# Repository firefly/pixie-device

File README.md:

Firefly Pixie: Hardware
=======================

The hardware design, schematics and PCB layouts for the Firefly
Pixie Hardware Wallet for Ethereum (and ilk).

- [Firmware](https://github.com/firefly/pixie-firmware)
- [Case](https://github.com/firefly/pixie-case)

See the [CHANGELOG](./CHANGELOG.md) for high-level changes
between board revisions.

Tech Specs
----------

- **Processor:** ESP32-C3 (32-bit RISC-V)
- **Speed:** 160Mhz
- **Memory:** 400kb RAM, 16Mb Flash, 4kb eFuse
- **Inputs:** 4x tactile buttons
- **Outputs:**
  - 240x240px IPS 1.3" display (16-bit color; RGB565)
  - 4x RGB LED (WS2812B; 24-bit color; GRB888)
- **Connectivity:**
  - USB-C (power + JTAG/CDC-ACM)
  - BLE

Contributing
------------

- To modify the files, use [KiCad](https://www.kicad.org) (open-source EDA application)
- Since the `git diff` involved in modifying these files is somewhat opaque, please start a discussion first, so any changes can be coordinated

Photos
-----------

See the [output](./output/) folder for rendered schematics, PCBs
and 3D renders along with photos of the various revisions.

License
-------

MIT License.

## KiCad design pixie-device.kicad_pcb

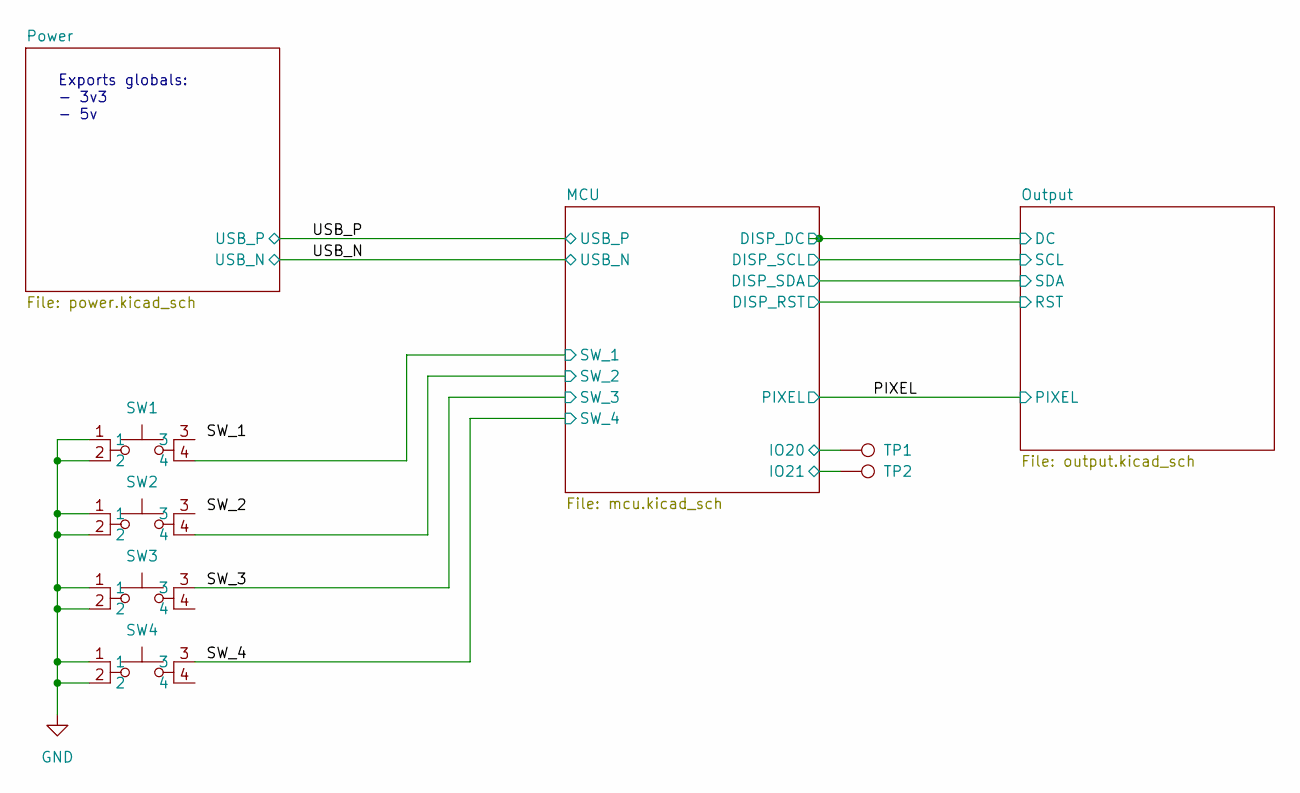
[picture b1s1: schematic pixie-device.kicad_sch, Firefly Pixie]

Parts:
SW1, SW2, SW3, SW4: button-oval; MPN C720479
TP1, TP2: TestPoint; TestPoint_Pad_D1.0mm

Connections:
/MCU/IO20: TP1.1; also elsewhere on the board
/MCU/IO21: TP2.1; also elsewhere on the board
/MCU/SW_1: SW1.4; also elsewhere on the board
/MCU/SW_2: SW2.4; also elsewhere on the board
/SW_3: SW3.3; also elsewhere on the board
/SW_4: SW4.3; also elsewhere on the board
GND: SW1.1, SW1.2, SW2.1, SW2.2, SW3.1, SW3.2, SW4.1, SW4.2; also elsewhere on the board

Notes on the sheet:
Exports globals: - 3v3 - 5v

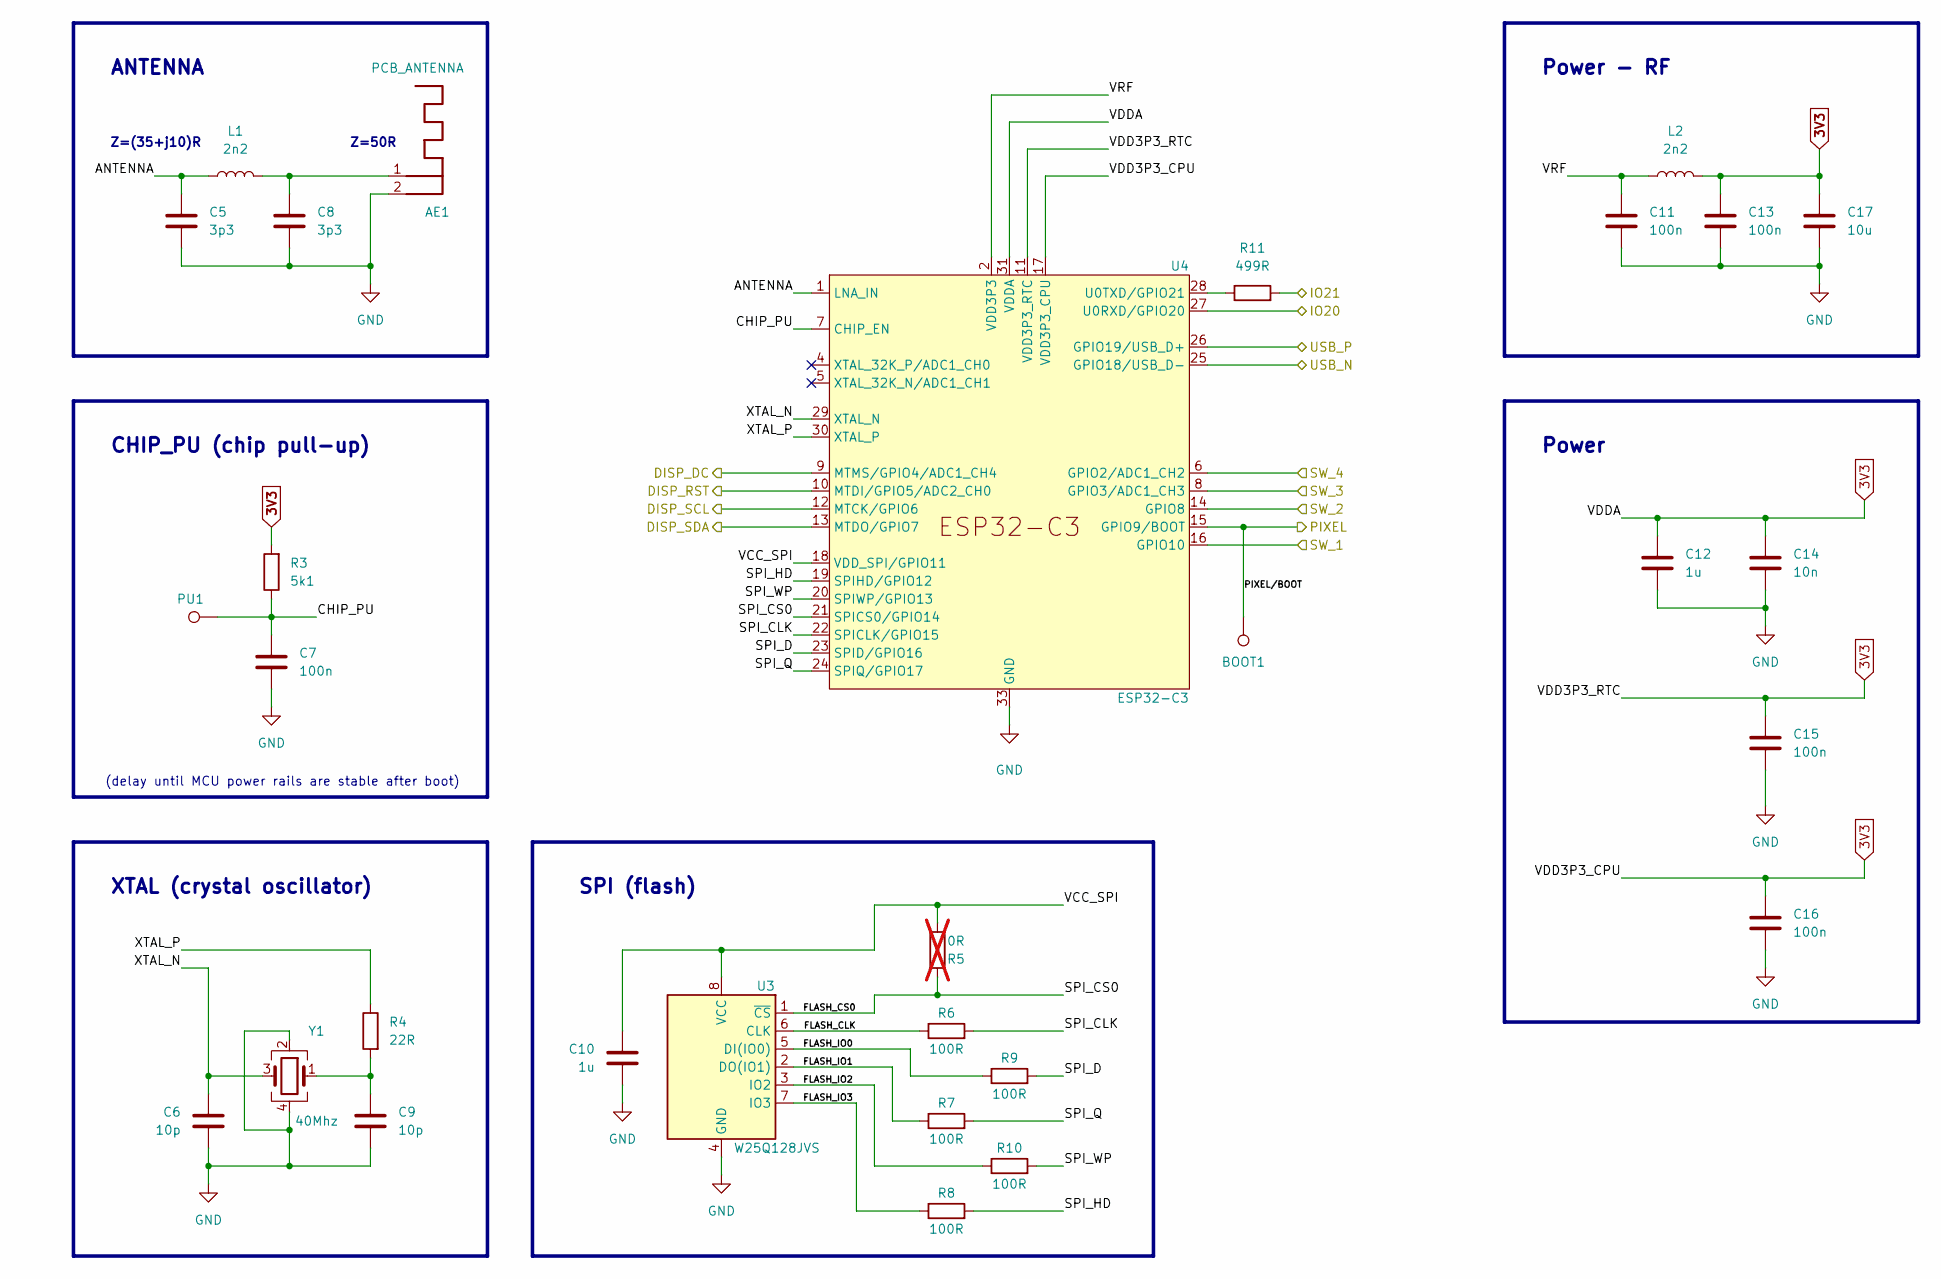
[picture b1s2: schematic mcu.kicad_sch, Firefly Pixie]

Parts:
AE1: PCB_ANTENNA; PCB_Antenna
BOOT1: TestPoint; TestPoint_Pad_D1.0mm
C5, C8: 3p3; C_0201_0603Metric; MPN C258460
C6, C9: 10p; C_0201_0603Metric; MPN C272871
C7, C11, C13, C15, C16: 100n; C_0201_0603Metric; MPN C284966
C10, C12: 1u; C_0201_0603Metric; MPN C170153
C14: 10n; C_0201_0603Metric; MPN C76941
C17: 10u; C_0402_1005Metric; MPN C315248
L1, L2: 2n2; L_0201_0603Metric; MPN C98041
PU1: TestPoint; TestPoint_Pad_D1.0mm
R3: 5k1; R_0201_0603Metric; MPN C274341
R4: 22R; R_0201_0603Metric; MPN C270355
R5: 0R; R_0201_0603Metric; not fitted
R6, R7, R8, R9, R10: 100R; R_0201_0603Metric; MPN C77623
R11: 499R; R_0201_0603Metric; MPN C4354889
U3: W25Q128JVS; SOIC-8_5.23x5.23mm_P1.27mm; MPN C97521
U4: ESP32-C3; QFN-32-1EP_5x5mm_P0.5mm_EP3.45x3.45mm; MPN C2838500
Y1: 40Mhz; crystal_2520; MPN_old C255973

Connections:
3V3: C12.1, C13.1, C14.1, C15.1, C16.1, C17.1, L2.2, R3.2, U4.11 (VDD3P3_RTC), U4.17 (VDD3P3_CPU), U4.31 (VDDA), U4.32 (VDDA); also elsewhere on the board
/MCU/ANTENNA: C5.1, L1.1, U4.1 (LNA_IN)
/MCU/CHIP_PU: C7.1, PU1.1, R3.1, U4.7 (CHIP_EN)
/MCU/DISP_DC: U4.9 (MTMS/GPIO4/ADC1_CH4); also elsewhere on the board
/MCU/DISP_RST: U4.10 (MTDI/GPIO5/ADC2_CH0); also elsewhere on the board
/MCU/DISP_SCL: U4.12 (MTCK/GPIO6); also elsewhere on the board
/MCU/DISP_SDA: U4.13 (MTDO/GPIO7); also elsewhere on the board
/MCU/FLASH_CLK: R6.1, U3.6 (CLK)
/MCU/FLASH_CS0: R5.2, U3.1 (~CS), U4.21 (SPICS0/GPIO14)
/MCU/FLASH_IO0: R9.1, U3.5 (DI(IO0))
/MCU/FLASH_IO1: R7.1, U3.2 (DO(IO1))
/MCU/FLASH_IO2: R10.1, U3.3 (IO2)
/MCU/FLASH_IO3: R8.1, U3.7 (IO3)
/MCU/IO20: U4.27 (U0RXD/GPIO20); also elsewhere on the board
/MCU/IO21: R11.2; also elsewhere on the board
/MCU/SPI_CLK: R6.2, U4.22 (SPICLK/GPIO15)
/MCU/SPI_D: R9.2, U4.23 (SPID/GPIO16)
/MCU/SPI_HD: R8.2, U4.19 (SPIHD/GPIO12)
/MCU/SPI_Q: R7.2, U4.24 (SPIQ/GPIO17)
/MCU/SPI_WP: R10.2, U4.20 (SPIWP/GPIO13)
/MCU/SW_1: U4.16 (GPIO10); also elsewhere on the board
/MCU/SW_2: U4.14 (GPIO8); also elsewhere on the board
/MCU/VCC_SPI: C10.1, R5.1, U3.8 (VCC), U4.18 (VDD_SPI/GPIO11)
/MCU/VRF: C11.1, L2.1, U4.2 (VDD3P3), U4.3 (VDD3P3)
/MCU/XTAL_N: C6.1, U4.29 (XTAL_N), Y1.3
/MCU/XTAL_P: R4.1, U4.30 (XTAL_P)
/PIXEL: BOOT1.1, U4.15 (GPIO9/BOOT); also elsewhere on the board
/SW_3: U4.8 (GPIO3/ADC1_CH3); also elsewhere on the board
/SW_4: U4.6 (GPIO2/ADC1_CH2); also elsewhere on the board
/USB_N: U4.25 (GPIO18/USB_D-); also elsewhere on the board
/USB_P: U4.26 (GPIO19/USB_D+); also elsewhere on the board
GND: AE1.2, C5.2, C6.2, C7.2, C8.2, C9.2, C10.2, C11.2, C12.2, C13.2, C14.2, C15.2, C16.2, C17.2, U3.4 (GND), U4.33 (GND), Y1.2, Y1.4; also elsewhere on the board
unnamed: AE1.1, C8.1, L1.2
unnamed: C9.1, R4.2, Y1.1
unnamed: R11.1, U4.28 (U0TXD/GPIO21)

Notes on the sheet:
Power - RF
Z=50R
XTAL (crystal oscillator)
Z=(35+j10)R
Power
SPI (flash)
(delay until MCU power rails are stable after boot)
ANTENNA
CHIP_PU (chip pull-up)

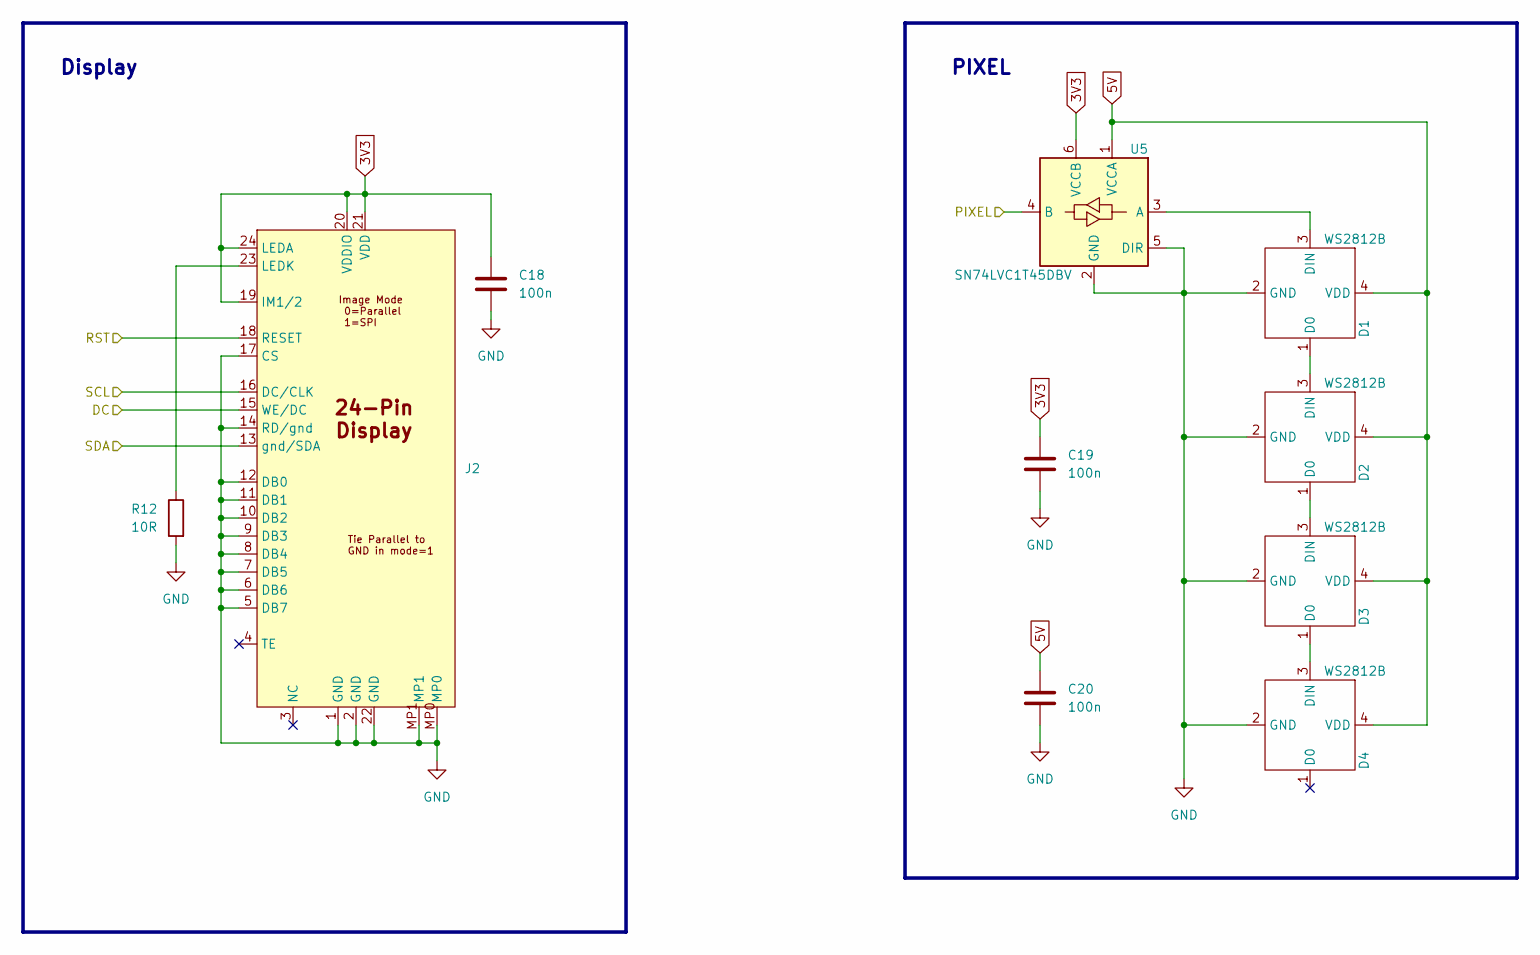
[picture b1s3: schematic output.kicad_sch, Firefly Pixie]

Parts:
C18, C19, C20: 100n; C_0201_0603Metric; MPN C284966
D1, D2, D3, D4: WS2812B; MPN C2976072
J2: JUSHUO_FPC_24; MPN C262669
R12: 10R; R_0201_0603Metric; MPN C304508
U5: SN74LVC1T45DBV; SOT-23-6; MPN C168856

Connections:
3V3: C18.1, C19.1, J2.19 (IM1/2), J2.20 (VDDIO), J2.21 (VDD), J2.24 (LEDA), U5.6 (VCCB); also elsewhere on the board
5V: C20.1, D1.4 (VDD), D2.4 (VDD), D3.4 (VDD), D4.4 (VDD), U5.1 (VCCA); also elsewhere on the board
/MCU/DISP_DC: J2.15 (WE/DC); also elsewhere on the board
/MCU/DISP_RST: J2.18 (RESET); also elsewhere on the board
/MCU/DISP_SCL: J2.16 (DC/CLK); also elsewhere on the board
/MCU/DISP_SDA: J2.13 (gnd/SDA); also elsewhere on the board
/PIXEL: U5.4 (B); also elsewhere on the board
GND: C18.2, C19.2, C20.2, D1.2 (GND), D2.2 (GND), D3.2 (GND), D4.2 (GND), J2.1 (GND), J2.2 (GND), J2.5 (DB7), J2.6 (DB6), J2.7 (DB5), J2.8 (DB4), J2.9 (DB3), J2.10 (DB2), J2.11 (DB1), J2.12 (DB0), J2.14 (RD/gnd), J2.17 (CS), J2.22 (GND), J2.MP0, J2.MP1, R12.2, U5.2 (GND), U5.5 (DIR); also elsewhere on the board
unnamed: D1.1 (D0), D2.3 (DIN)
unnamed: D1.3 (DIN), U5.3 (A)
unnamed: D2.1 (D0), D3.3 (DIN)
unnamed: D3.1 (D0), D4.3 (DIN)
unnamed: J2.23 (LEDK), R12.1

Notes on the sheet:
Display
PIXEL

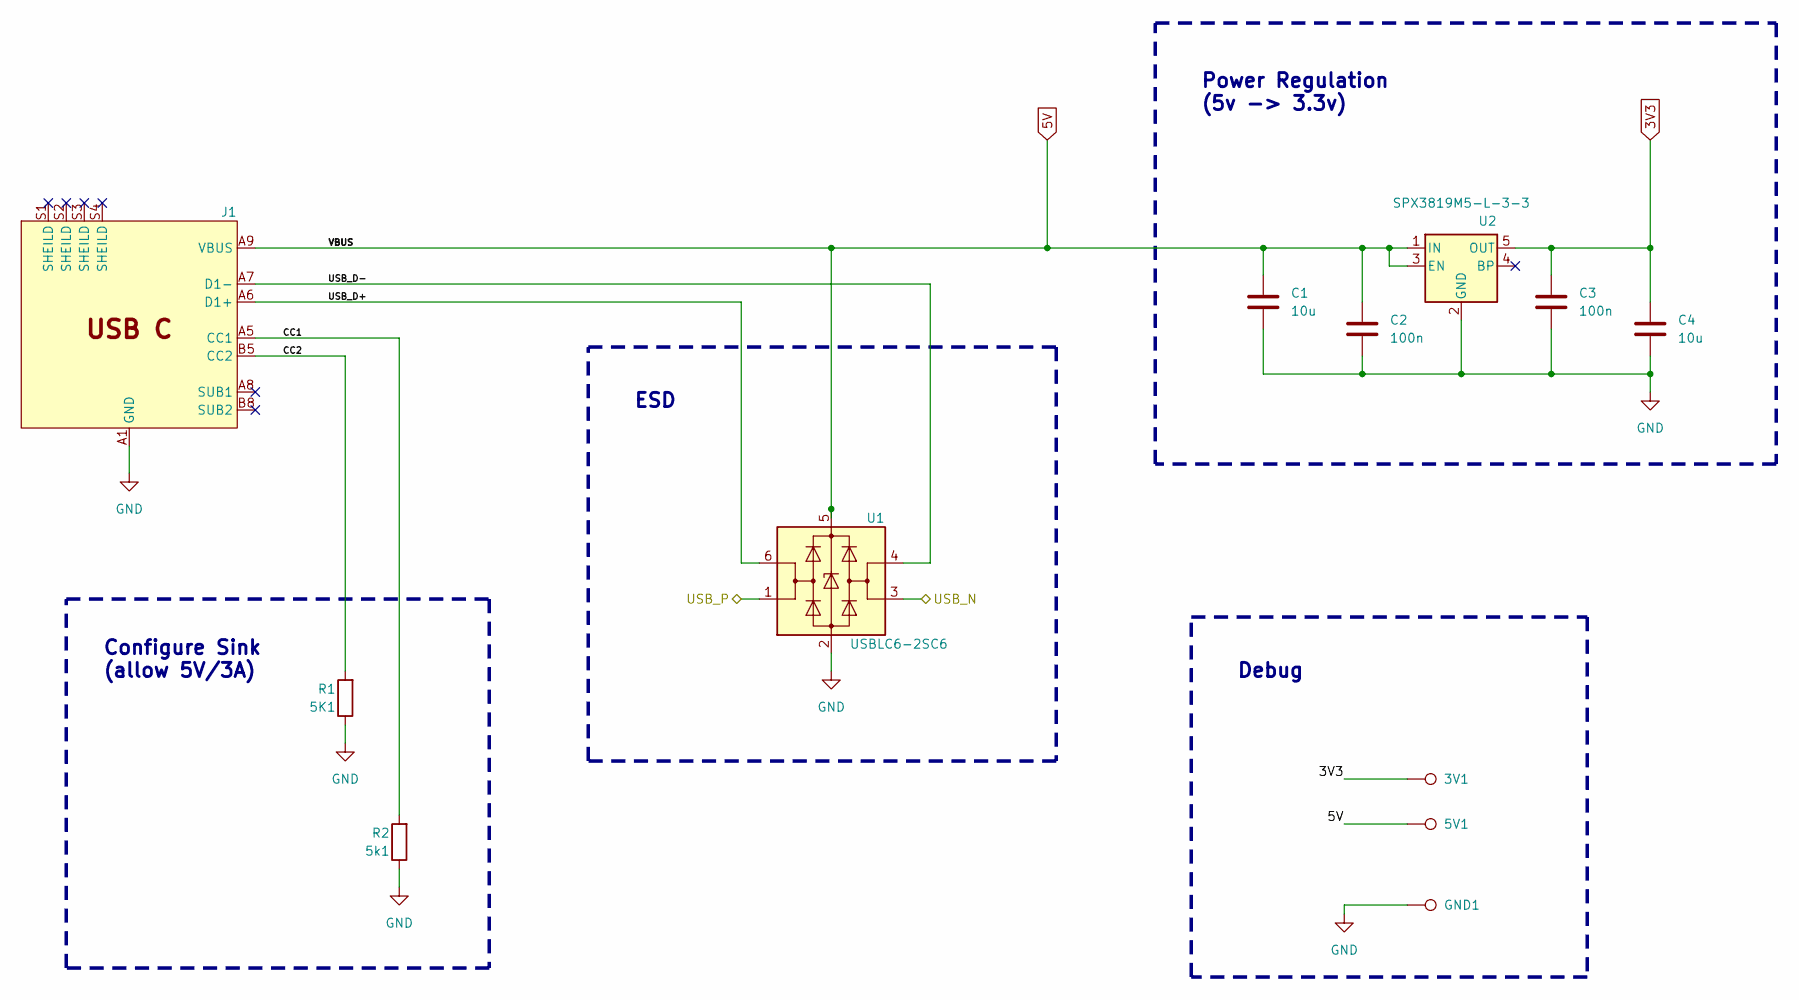
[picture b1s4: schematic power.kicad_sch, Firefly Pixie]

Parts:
3V1, 5V1: TestPoint; TestPoint_Pad_1.0x1.0mm
C1, C4: 10u; C_0402_1005Metric; MPN C315248
C2, C3: 100n; C_0201_0603Metric; MPN C284966
GND1: TestPoint; TestPoint_Pad_1.0x1.0mm
J1: USB_C_SINK; MPN C2906289
R1: 5K1; R_0201_0603Metric; MPN C274341
R2: 5k1; R_0201_0603Metric; MPN C274341
U1: USBLC6-2SC6; SOT-563; MPN C2827693
U2: SPX3819M5-L-3-3; SOT-23-5; MPN C5370980

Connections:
3V3: 3V1.1, C3.1, C4.1, U2.5 (OUT); also elsewhere on the board
5V: 5V1.1, C1.1, C2.1, J1.A4 (VBUS), J1.A9 (VBUS), J1.B4 (VBUS), J1.B9 (VBUS), U1.5 (VBUS), U2.1 (IN), U2.3 (EN); also elsewhere on the board
/Power/CC1: J1.A5 (CC1), R2.2
/Power/CC2: J1.B5 (CC2), R1.2
/Power/USB_D+: J1.A6 (D1+), J1.B6 (D2+), U1.6 (I/O1)
/Power/USB_D-: J1.A7 (D1-), J1.B7 (D2-), U1.4 (I/O2)
/USB_N: U1.3 (I/O2); also elsewhere on the board
/USB_P: U1.1 (I/O1); also elsewhere on the board
GND: C1.2, C2.2, C3.2, C4.2, GND1.1, J1.A1 (GND), J1.A12 (GND), J1.B1 (GND), J1.B12 (GND), R1.1, R2.1, U1.2 (GND), U2.2 (GND); also elsewhere on the board

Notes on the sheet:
Power Regulation (5v -> 3.3v)
Configure Sink (allow 5V/3A)
ESD
Debug

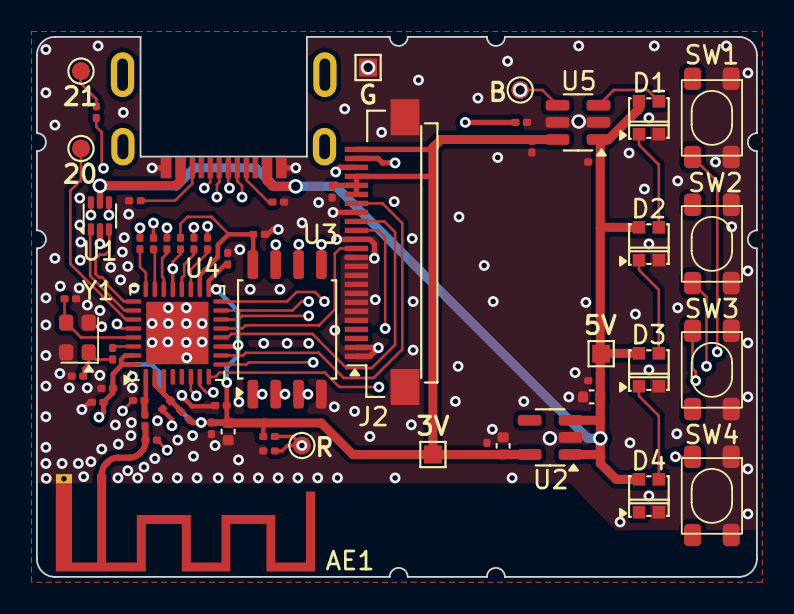
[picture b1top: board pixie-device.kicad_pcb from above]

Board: 4 copper layers, 40.0 x 30.0 mm, 58 parts (0 on the bottom side), 45 nets.

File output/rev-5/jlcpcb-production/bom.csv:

Designator,Footprint,Quantity,Value,LCSC Part #
"C1, C17, C4",0402,3,10u,C315248
"C10, C12",0201,2,1u,C170153
"C11, C13, C15, C16, C18, C19, C2, C20, C3, C7",0201,10,100n,C284966
C14,0201,1,10n,C76941
"C5, C8",0201,2,3p3,C258460
"C6, C9",0201,2,10p,C272871
"D1, D2, D3, D4",WS2812B,4,WS2812B,C2976072
J1,USB_C_SINK,1,~,C2906289
J2,JUSHUO_FPC_24,1,~,C262669
"L1, L2",0201,2,2n2,C98041
"R1, R2, R3",0201,3,5K1,C274341
"R10, R6, R7, R8, R9",0201,5,100R,C77623
R11,0201,1,499R,C4354889
R12,0201,1,10R,C304508
R4,0201,1,22R,C270355
"SW1, SW2, SW3, SW4",button-oval,4,~,C720479
U1,SOT-563,1,USBLC6-2SC6,C2827693
U2,SOT-23-5,1,SPX3819M5-L-3-3,C5370980
U3,SOIC-8_5.23x5.23mm_P1.27mm,1,W25Q128JVS,C97521
U4,QFN-32-1EP_5x5mm_P0.5mm_EP3.1x3.1mm,1,ESP32-C3,C2838500
U5,SOT-23-6,1,SN74LVC1T45DBV,C168856
Y1,Crystal_SMD_2520-4Pin_2.5x2.0mm,1,40Mhz,C409424

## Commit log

2023-10-12 Initial code drop.
2023-10-12 Added screenshots.
2023-10-12 Made U4 ref visible.
2023-10-14 Check-in before trying ESP32-C3-F4.
2023-10-24 Checking in before updating against ESP32-C3-WROOM-02 designs.
2023-12-09 JLCPCB Submit
2023-12-09 Updated readme and images.
2023-12-09 Added missing sub-sheets.
2024-04-06 Checking in before submitting rev.5 to JLCPCB.
2024-04-06 Updated readme to reflect rev.5 features.
2024-04-23 Added 3D models for button and LED.
2024-04-23 Added changelog.
2024-04-23 Updated changes for KiCAD 8.
2024-04-23 Added gitignore for 3D models SketchUp scratch files.
2024-04-23 Renamed project from pixie-rev-4 to pixie-device.
2024-04-24 Move output files.
2024-04-24 Added KiCad components.
2024-04-24 Remove dead file references to 3d models.
2024-04-24 Fix image paths in rev-4 output.
2024-04-24 Added Firefly KiCad component libraries to project.
2024-04-24 Updated readme.
2024-04-24 Fix readme.
2024-04-24 Update readme panel info.
2024-04-24 Updated components for KiCad 8.
2024-04-24 Use ESP suggested C3 footprint and update for KiCad 8.
2024-04-24 Added USB-C sink 3D model.
2024-04-24 Moved GPIO 20 and 21 around.
2024-04-25 Removed old unused footprints.
2024-04-25 Added new-style pin 1 designator to footprints.
2024-04-25 Added keywords to footprints.
2024-04-25 Added texture for USB-C 3D model.
2024-04-25 Tweaked materials for 3D models.
2024-04-25 Tweaked placements; GPIO 20 and 21.
2024-04-25 docs: updated readme language
2024-04-25 Updated history output files.
2024-04-25 Added some rev-6 output files.
2024-04-25 docs: focus readme on device renders.
2024-04-25 Found old rev-2 files to generate historic output.
2024-04-30 Added panelization using KiKit.
2024-04-30 admin: ignore intermediate panelize files
2024-04-30 Added renders of the panel
2024-04-30 Fixed dimension in Panel readme.
2024-04-30 Changed panel to 2x3 layout.
2024-04-30 Added historic JLCPCB production files.
2024-04-30 Fixed historic schematics lost during export.
2024-06-08 Nove mouse bite tabs for better panel strength.
2024-07-09 Move buttons and LEDs 2mm right to accomodate thumb space between the screen.
2024-07-09 Adjust the mousebites.
2024-07-09 Updated panelize gitignore.
2024-07-09 docs: updated readme
2024-07-09 Added rev.6 renders.
2024-07-09 Added prodction files used for the rev.6.
